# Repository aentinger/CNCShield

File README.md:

💾 CNC Shield
=============

# 📸 Image

# 📂 Description

Until very recently the operation of CNC milling machines was reserved mainly for companies and individuals with large budget. However, in the last couple of years, an increasing trend towards self-made (DIY) CNC-milling machines could be observed. As a result from this observation LXRobotics developed the CNC Shield. The CNC-Shield is based on the grbl project, which allows the processing of gcode-control commands and generation of stepper motor control signals for a 3-axis CNC-milling machine with an Arduino Uno.

In order to demonstrate how easy a normal mill can be converted into a CNC mill we decided to convert the Proxxon MF70, a very popular milling machine amongst RC enthusiasts, into a full-fledged CNC-milling machine by using our CNC shield. The conversion with all necessary steps is well documented on our blog. Furthermore, extensive tutorials allow easy integration of our CNC  shields in any DIY-CNC project.

**Features**

* Control of 3 bipolar stepper motors with 2.5 A phase current at a maximum of 35 V (e.g.: NEMA17)
* Milling motor and coolant pump can be turned on/off via relays
* Limit switch for X, Y and Z-axis can be attached
* Cycle Start/Resume, Feed Hold and Reset/Abort switches can be attached
* grbl-compatible
* High qualits screw terminals for stable and durable connection of cables to the board
* 8A Fuse on board

Note
* Active cooling of the stepper motor driver is recommended.

# 🎥 [Video](images/cnc_shield_demo.mp4)

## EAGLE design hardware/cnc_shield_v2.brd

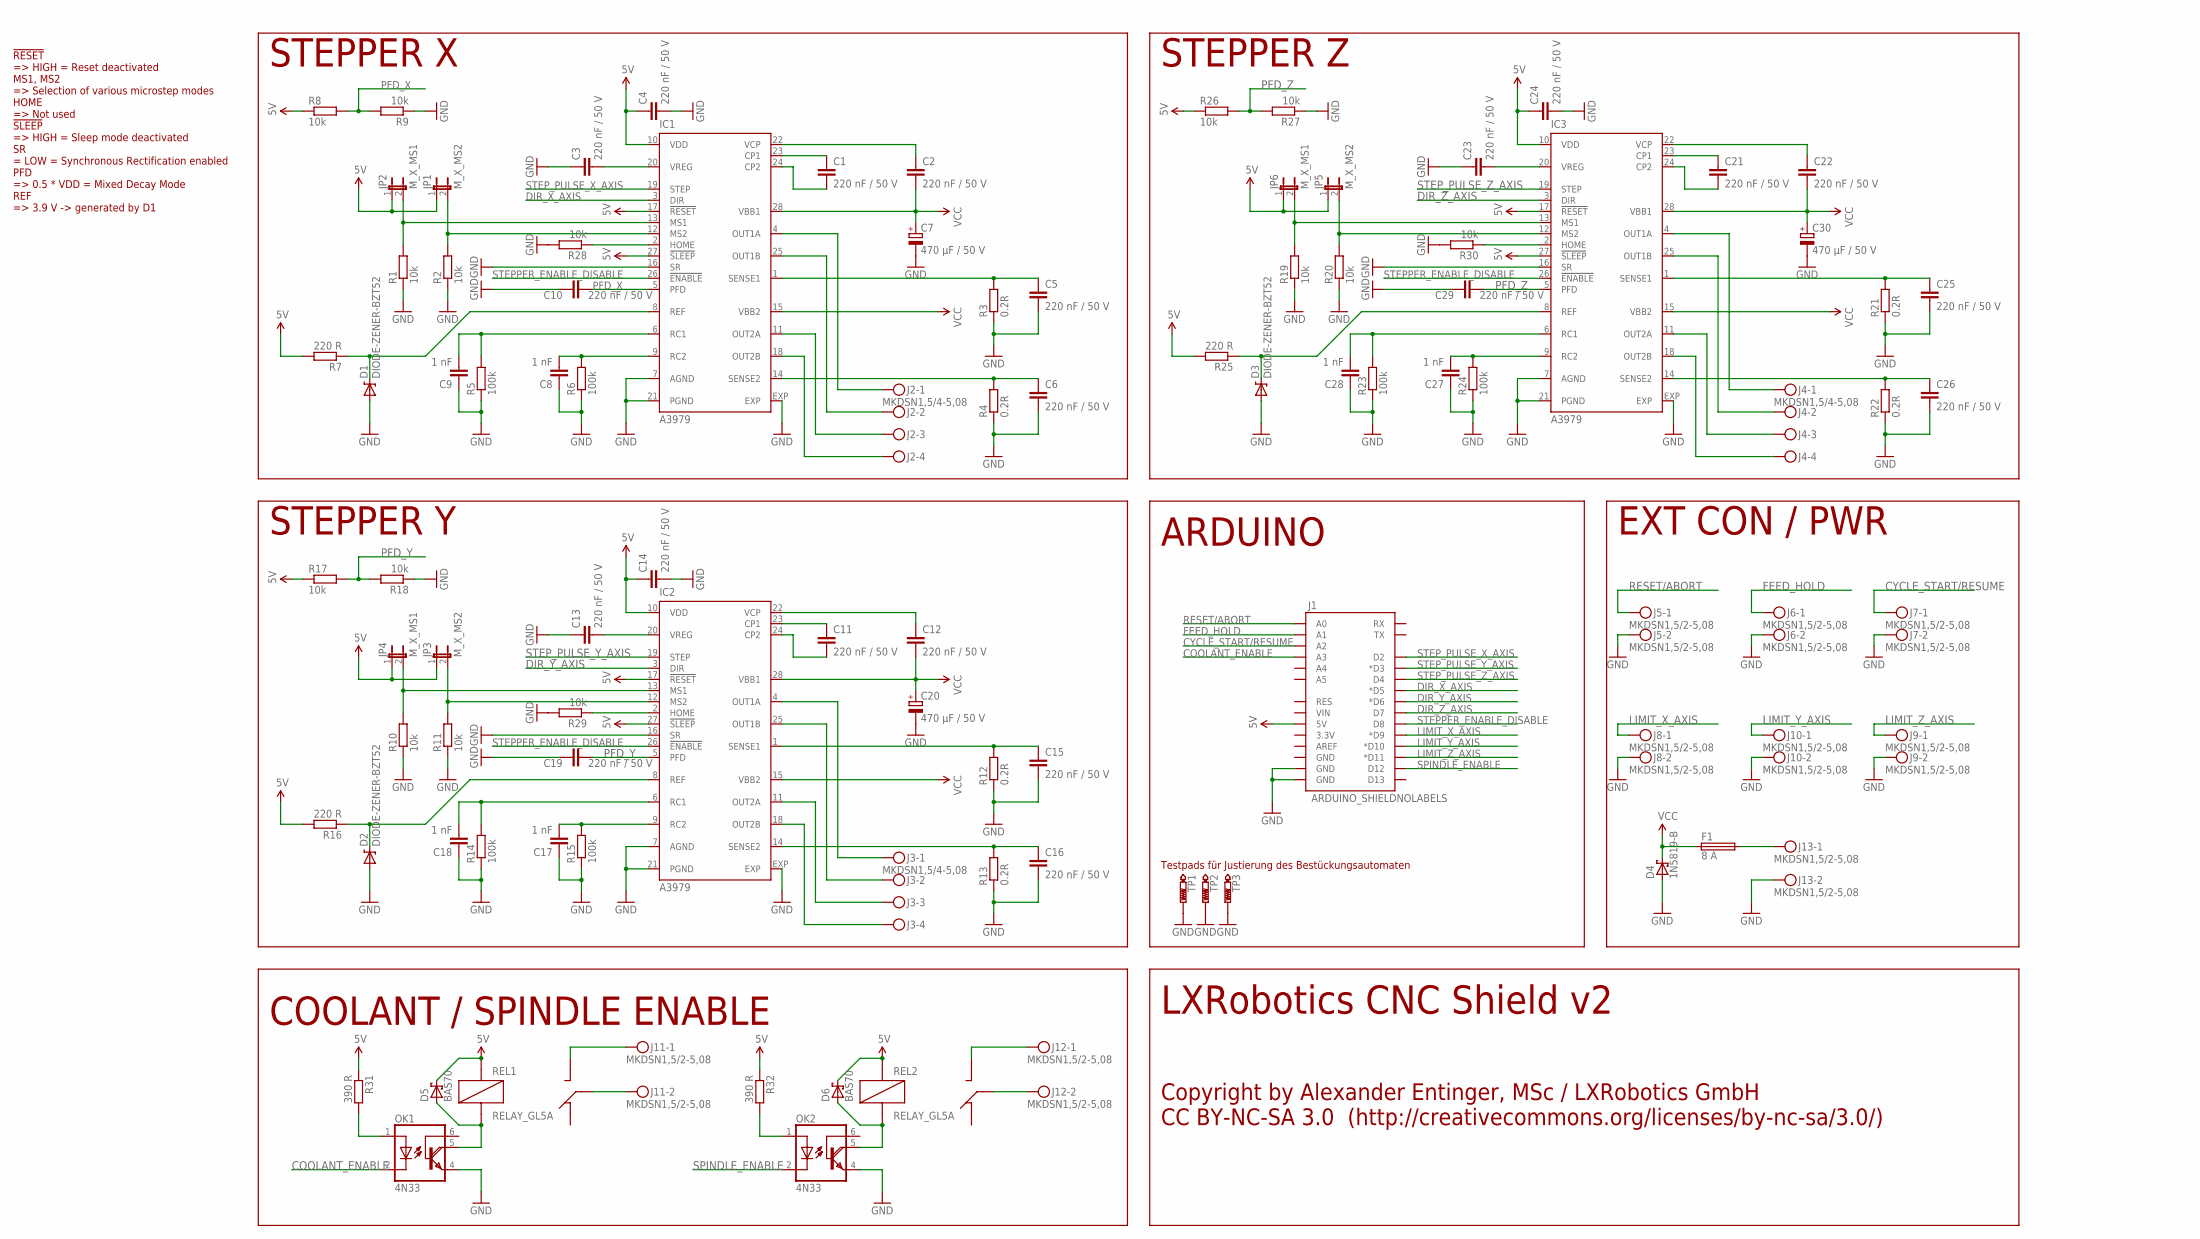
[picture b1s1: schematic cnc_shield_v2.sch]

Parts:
C1, C2, C3, C4, C5, C6, C10, C11, C12, C13, C14, C15, C16, C19, C21, C22, C23, C24, C25, C26, C29: 220 nF / 50 V; C0805K
C7, C20, C30: 470 µF / 50 V; E5-13
C8, C9, C17, C18, C27, C28: 1 nF; C0805K
D1, D2, D3: DIODE-ZENER-BZT52; SOD-323
D4: 1N5819-B; DO41-7.6
D5, D6: BAS70; SOT23
F1: 8 A; SH22,5
IC1, IC2, IC3: A3979; TSSOP28
J1: ARDUINO_SHIELDNOLABELS; DUEMILANOVE_SHIELD_NOLABELS
J2, J3, J4: MKDSN1,5/4-5,08
J5, J6, J7, J8, J9, J10, J11, J12, J13: MKDSN1,5/2-5,08
JP1, JP3, JP5: M_X_MS2; JP1
JP2, JP4, JP6: M_X_MS1; JP1
OK1, OK2: 4N33; DIL06
R1, R2, R8, R9, R10, R11, R17, R18, R19, R20, R26, R27, R28, R29, R30: 10k; R0805
R3, R4, R12, R13, R21, R22: 0.2R; R2512
R5, R6, R14, R15, R23, R24: 100k; R0805
R7, R16, R25: 220 R; R0805
R31, R32: 390 R; R0805
REL1, REL2: RELAY_GL5A
TP1, TP2, TP3: PTR1B1,27; B1,27

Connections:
5V: C4.1, C14.1, C24.1, D5.3 (C), D6.3 (C), IC1.10 (VDD), IC1.17 (!RESET), IC1.27 (!SLEEP), IC2.10 (VDD), IC2.17 (!RESET), IC2.27 (!SLEEP), IC3.10 (VDD), IC3.17 (!RESET), IC3.27 (!SLEEP), J1.5V, JP1.1, JP2.1, JP3.1, JP4.1, JP5.1, JP6.1, R7.2, R8.1, R16.2, R17.1, R25.2, R26.1, R31.1, R32.1, REL1.R2 (R2_COIL1), REL2.R2 (R2_COIL1)
COOLANT_ENABLE: J1.A3, OK1.2 (C)
CYCLE_START/RESUME: J1.A2, J7.1
DIR_X_AXIS: IC1.3 (DIR), J1.D5 (*D5)
DIR_Y_AXIS: IC2.3 (DIR), J1.D6 (*D6)
DIR_Z_AXIS: IC3.3 (DIR), J1.D7
FEED_HOLD: J1.A1, J6.1
GND: C3.1, C4.2, C5.2, C6.2, C7.-, C8.1, C9.1, C10.1, C13.1, C14.2, C15.2, C16.2, C17.1, C18.1, C19.1, C20.-, C23.1, C24.2, C25.2, C26.2, C27.1, C28.1, C29.1, C30.-, D1.2 (A), D2.2 (A), D3.2 (A), D4.A, IC1.7 (AGND), IC1.16 (SR), IC1.21 (PGND), IC1.EXP, IC2.7 (AGND), IC2.16 (SR), IC2.21 (PGND), IC2.EXP, IC3.7 (AGND), IC3.16 (SR), IC3.21 (PGND), IC3.EXP, J1.GND@0 (GND), J1.GND@1 (GND), J5.2, J6.2, J7.2, J8.2, J9.2, J10.2, J13.2, OK1.4 (E), OK2.4 (E), R1.1, R2.1, R3.1, R4.1, R5.1, R6.1, R9.1, R10.1, R11.1, R12.1, R13.1, R14.1, R15.1, R18.1, R19.1, R20.1, R21.1, R22.1, R23.1, R24.1, R27.1, R28.2, R29.2, R30.2, TP1.TP, TP2.TP, TP3.TP
LIMIT_X_AXIS: J1.D9 (*D9), J8.1
LIMIT_Y_AXIS: J1.D10 (*D10), J10.1
LIMIT_Z_AXIS: J1.D11 (*D11), J9.1
unnamed: C1.1, IC1.23 (CP1)
unnamed: C1.2, IC1.24 (CP2)
unnamed: C2.1, IC1.22 (VCP)
unnamed: IC1.12 (MS2), JP1.2, R2.2
unnamed: IC1.13 (MS1), JP2.2, R1.2
unnamed: C3.2, IC1.20 (VREG)
unnamed: C5.1, IC1.1 (SENSE1), R3.2
unnamed: C6.1, IC1.14 (SENSE2), R4.2
unnamed: IC1.18 (OUT2B), J2.4
unnamed: IC1.11 (OUT2A), J2.3
unnamed: IC1.25 (OUT1B), J2.2
unnamed: IC1.4 (OUT1A), J2.1
unnamed: D1.1 (C), IC1.8 (REF), R7.1
unnamed: C11.1, IC2.23 (CP1)
unnamed: C8.2, IC1.9 (RC2), R6.2
unnamed: C9.2, IC1.6 (RC1), R5.2
unnamed: C11.2, IC2.24 (CP2)
unnamed: C12.1, IC2.22 (VCP)
unnamed: C13.2, IC2.20 (VREG)
unnamed: IC2.12 (MS2), JP3.2, R11.2
unnamed: IC2.13 (MS1), JP4.2, R10.2
unnamed: C15.1, IC2.1 (SENSE1), R12.2
unnamed: C16.1, IC2.14 (SENSE2), R13.2
unnamed: IC2.18 (OUT2B), J3.4
unnamed: IC2.11 (OUT2A), J3.3
unnamed: IC2.25 (OUT1B), J3.2
unnamed: IC2.4 (OUT1A), J3.1
unnamed: C17.2, IC2.9 (RC2), R15.2
unnamed: C18.2, IC2.6 (RC1), R14.2
unnamed: D2.1 (C), IC2.8 (REF), R16.1
unnamed: C21.1, IC3.23 (CP1)
unnamed: C21.2, IC3.24 (CP2)
unnamed: C22.1, IC3.22 (VCP)
unnamed: C23.2, IC3.20 (VREG)
unnamed: IC3.12 (MS2), JP5.2, R20.2
unnamed: IC3.13 (MS1), JP6.2, R19.2
unnamed: C25.1, IC3.1 (SENSE1), R21.2
unnamed: C26.1, IC3.14 (SENSE2), R22.2
unnamed: IC3.18 (OUT2B), J4.4
unnamed: IC3.11 (OUT2A), J4.3
unnamed: IC3.25 (OUT1B), J4.2
unnamed: IC3.4 (OUT1A), J4.1
unnamed: C27.2, IC3.9 (RC2), R24.2
unnamed: C28.2, IC3.6 (RC1), R23.2
unnamed: D3.1 (C), IC3.8 (REF), R25.1
unnamed: IC2.2 (HOME), R29.1
unnamed: IC1.2 (HOME), R28.1
unnamed: IC3.2 (HOME), R30.1
unnamed: D5.1 (A), OK1.5 (COL), REL1.R5 (R5_COIL2)
unnamed: OK1.1 (A), R31.2
unnamed: F1.2, J13.1
unnamed: J11.1, REL1.R3 (R3_SW)
unnamed: J11.2, REL1.R1 (R1_COMMON)
unnamed: D6.1 (A), OK2.5 (COL), REL2.R5 (R5_COIL2)
unnamed: OK2.1 (A), R32.2
unnamed: J12.1, REL2.R3 (R3_SW)
unnamed: J12.2, REL2.R1 (R1_COMMON)
PFD_X: C10.2, IC1.5 (PFD), R8.2, R9.2
PFD_Y: C19.2, IC2.5 (PFD), R17.2, R18.2
PFD_Z: C29.2, IC3.5 (PFD), R26.2, R27.2
RESET/ABORT: J1.A0, J5.1
SPINDLE_ENABLE: J1.D12, OK2.2 (C)
STEPPER_ENABLE_DISABLE: IC1.26 (!ENABLE), IC2.26 (!ENABLE), IC3.26 (!ENABLE), J1.D8
STEP_PULSE_X_AXIS: IC1.19 (STEP), J1.D2
STEP_PULSE_Y_AXIS: IC2.19 (STEP), J1.D3 (*D3)
STEP_PULSE_Z_AXIS: IC3.19 (STEP), J1.D4
VCC: C2.2, C7.+, C12.2, C20.+, C22.2, C30.+, D4.C, F1.1, IC1.15 (VBB2), IC1.28 (VBB1), IC2.15 (VBB2), IC2.28 (VBB1), IC3.15 (VBB2), IC3.28 (VBB1)

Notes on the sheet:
!RESET => HIGH = Reset deactivated MS1, MS2 => Selection of various microstep modes HOME => Not used !SLEEP => HIGH = Sleep mode deactivated SR = LOW = Synchronous Rectification enabled PFD => 0.5 * VDD = Mixed Decay Mode REF => 3.9 V -> generated by D1
STEPPER X
STEPPER Y
STEPPER Z
ARDUINO
EXT CON / PWR
COOLANT / SPINDLE ENABLE
LXRobotics CNC Shield v2
Copyright by Alexander Entinger, MSc / LXRobotics GmbH CC BY-NC-SA 3.0 (http://creativecommons.org/licenses/by-nc-sa/3.0/)
Testpads für Justierung des Bestückungsautomaten

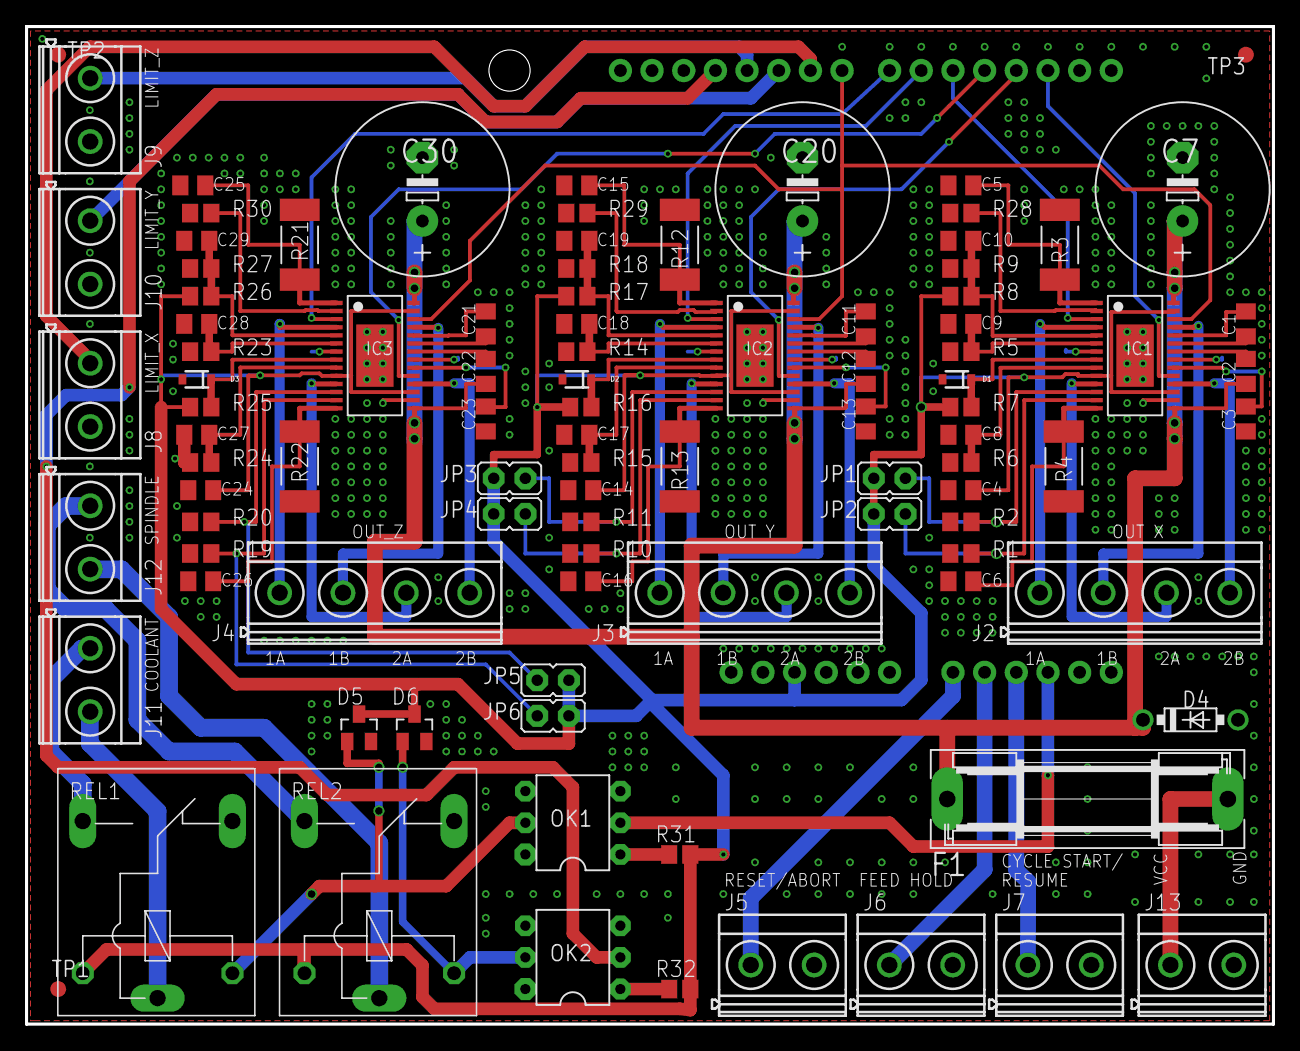
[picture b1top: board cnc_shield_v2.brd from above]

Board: 2 copper layers, 100.0 x 80.0 mm, 98 parts (0 on the bottom side), 78 nets.

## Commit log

2014-07-25 initial checkin of cnc shield repository
2014-07-31 adding 0.9 hex and renaming 0.8
2014-07-31 deleting grbl.hex (old 0.8 version)
2014-09-17 replacing grbl_v_0_9.hex with latest 0.9 version
2015-03-24 adding v2 version of cnc schield schematic
2017-06-27 Adding hardware + images
2025-03-26 Add video of CNC shield demo.
2025-03-26 Add BOM.
2025-03-26 Pretty up README.
2025-03-26 Use relative link.

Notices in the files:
README.md:
License: CC BY-NC-SA 4.0
parts and their libraries:
SparkFun-Boards: Licensing: CC v3.0 Share-Alike You are welcome to use this library for commercial purposes.
